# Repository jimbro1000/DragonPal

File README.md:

# PAL VIDEO BOARD FOR DRAGON 32 RECREATION Rev 3 #

To further improve video quality on the Dragon 32 this
board completely isolates the video circuits from the rest
of the Dragon by making it a plugin. This also means that
only a single version of the Dragon 32 board is needed to
provide a PAL or NTSC solution.

## Progress ##

This is a complete first hack at the design, while the
schematics are trusted the layout and organisation of the
line pulse logic is very much experimental.

The clock generator and analogue circuits are completely
isolated. The ground plane on the analogue side of the board 
is as complete and uniform as possible.

## To Do ##

Adopt the Dragon 64 voltage bias circuit for the output
signal

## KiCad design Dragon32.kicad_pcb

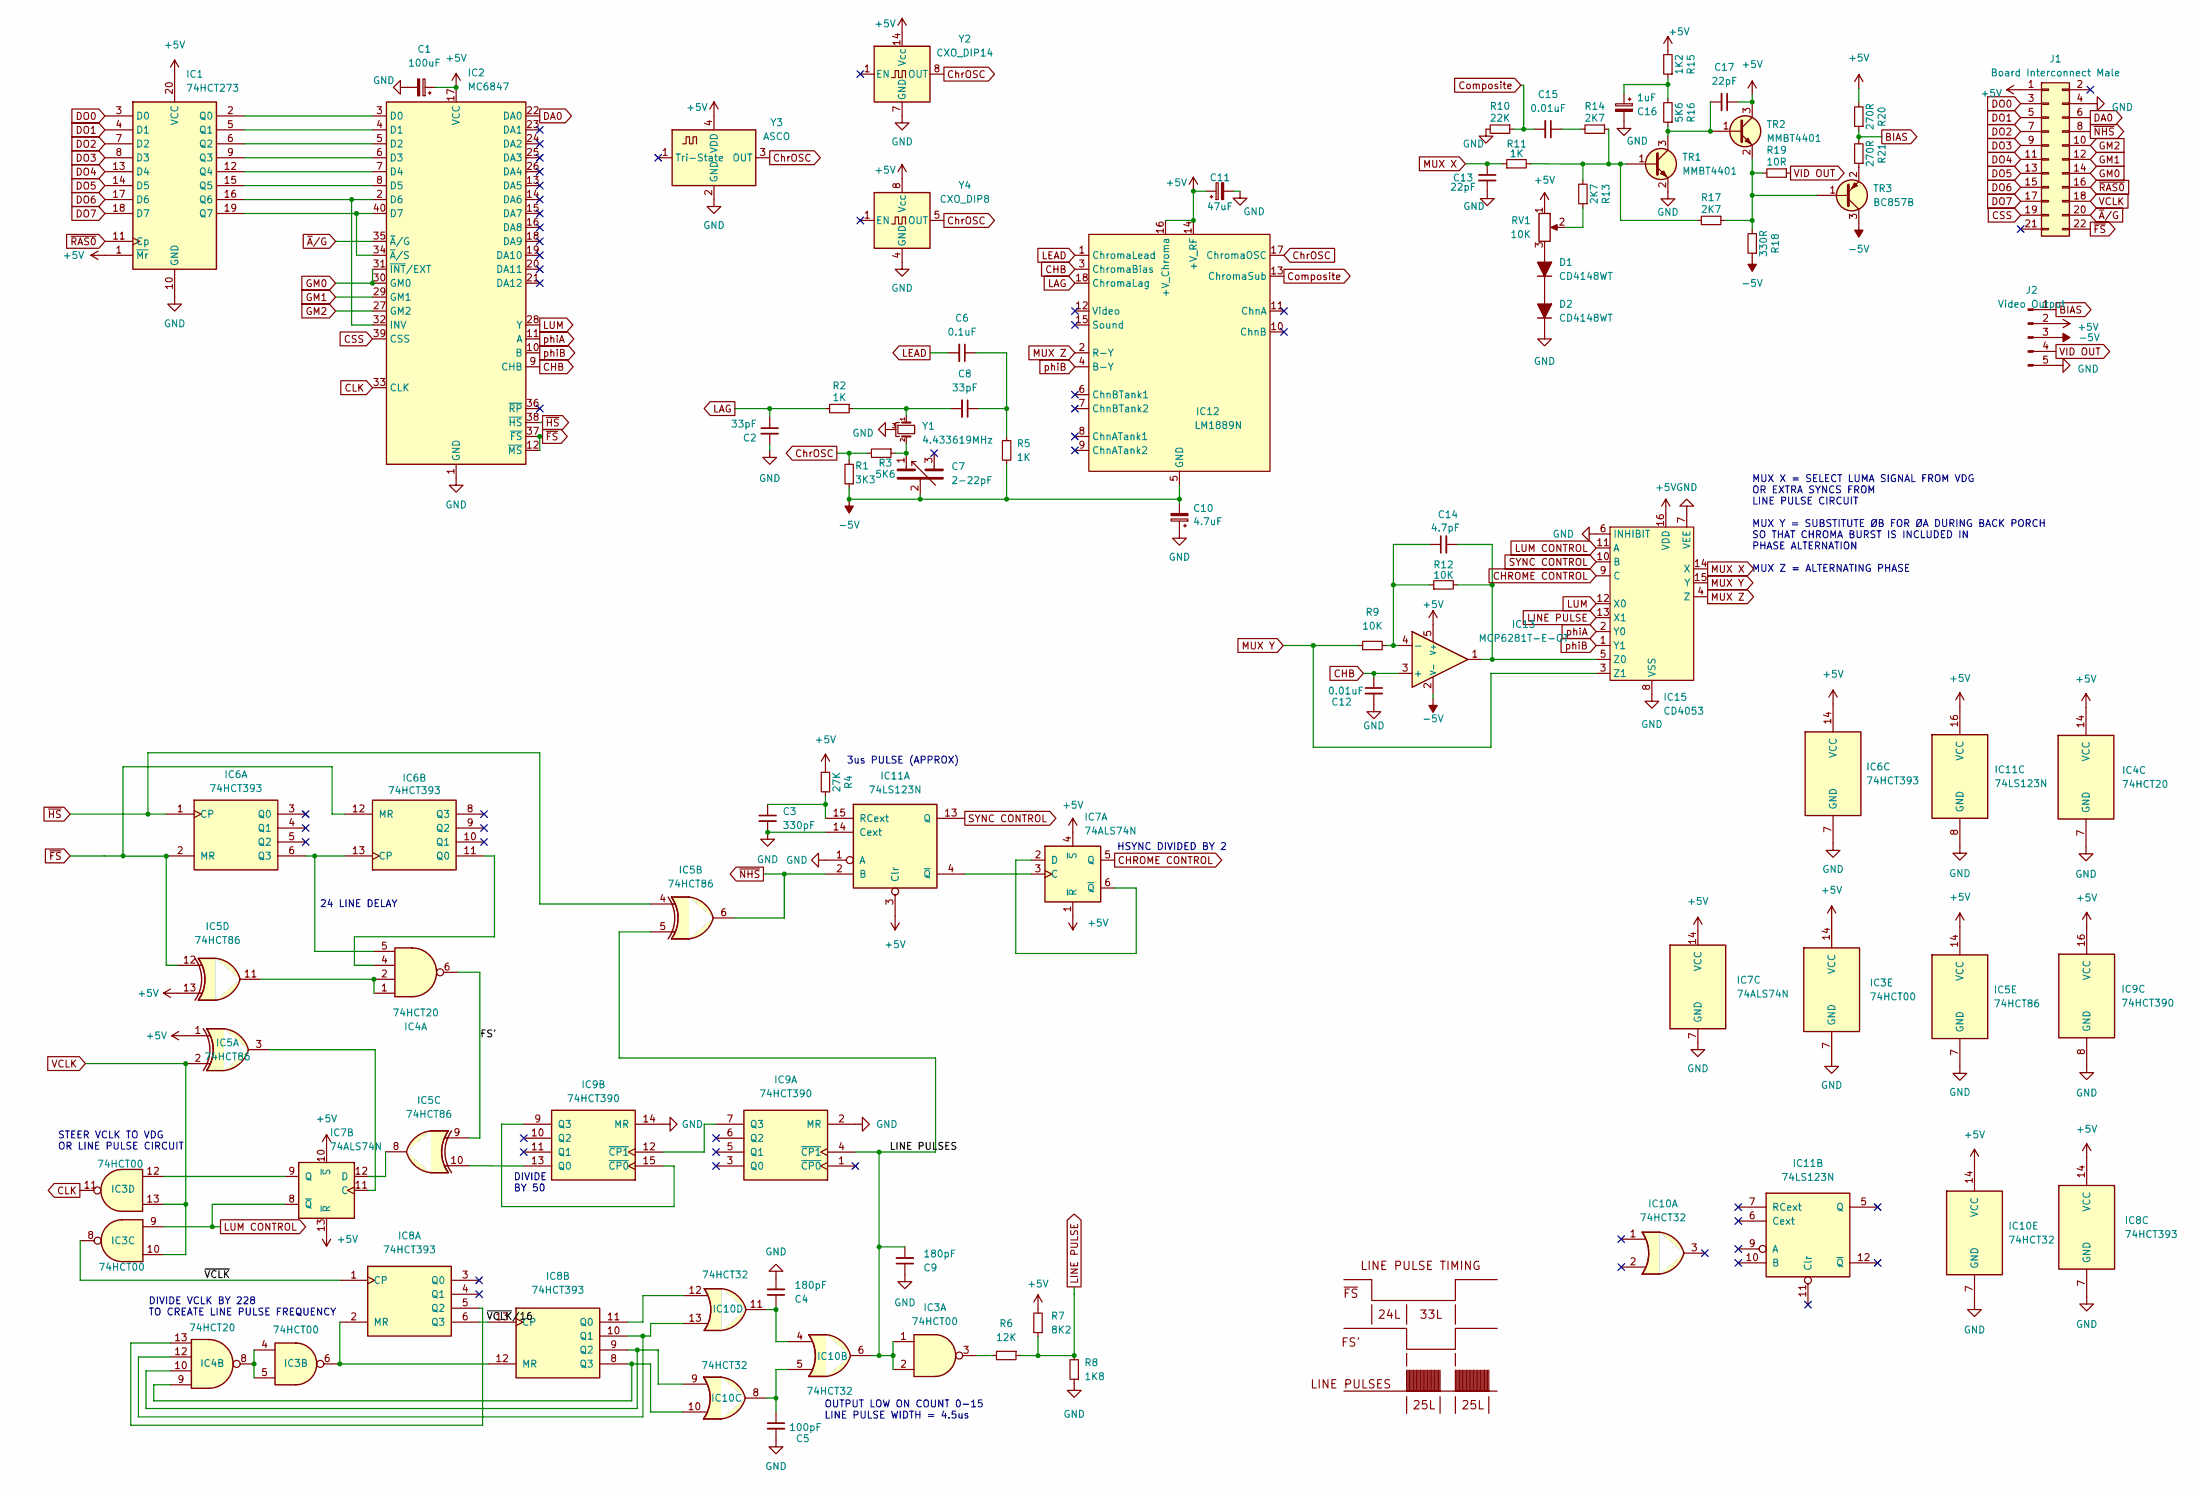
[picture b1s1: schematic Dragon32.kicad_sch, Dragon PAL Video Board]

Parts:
C1: 100uF; CP_Elec_6.3x5.8; DigiKey 732-8598-1-ND
C2, C8: 33pF; C_0603_1608Metric; LCSC C1663
C3: 330pF; C_0603_1608Metric; LCSC C1664
C4, C9: 180pF; C_0805_2012Metric_Pad1.18x1.45mm_HandSolder; DigiKey BC1016CT-ND
C5: 100pF; C_0805_2012Metric_Pad1.18x1.45mm_HandSolder; DigiKey 399-C316C101J5G5TA7303CT-ND
C6: 0.1uF; C_0805_2012Metric_Pad1.18x1.45mm_HandSolder; DigiKey BC1101CT-ND
C7: 2-22pF; Trimmer-7.5mm
C10: 4.7uF; CP_EIA-3528-15_AVX-H; DigiKey 478-3886-1-ND
C11: 47uF; CP_EIA-3528-15_AVX-H; DigiKey 478-11463-1-ND
C12, C15: 0.01uF; C_0805_2012Metric_Pad1.18x1.45mm_HandSolder; DigiKey BC2662CT-ND
C13, C17: 22pF; C_0805_2012Metric_Pad1.18x1.45mm_HandSolder; DigiKey 399-13930-1-ND
C14: 4.7pF; C_0603_1608Metric; DigiKey 445-180473-1-ND
C16: 1uF; CP_Elec_4x5.4; DigiKey 732-8966-1-ND
D1, D2: CD4148WT; D_0603_1608Metric; LCSC C30584800
IC1: 74HCT273; TSSOP-20_4.4x6.5mm_P0.65mm; DigiKey 296-8409-1-ND
IC2: MC6847; DIP-40_W15.24mm; LCSC C72123
IC3: 74HCT00; SOIC-14_3.9x8.7mm_P1.27mm; DigiKey 296-1626-ND
IC4: 74HCT20; SOIC-14_3.9x8.7mm_P1.27mm; DigiKey 296-3670-5-ND
IC5: 74HCT86; SOIC-14_3.9x8.7mm_P1.27mm; DigiKey 296-1669-5-ND
IC6, IC8: 74HCT393; SOIC-14_3.9x8.7mm_P1.27mm; DigiKey 296-14556-1-ND
IC7: 74ALS74N; SOIC-14_3.9x8.7mm_P1.27mm; DigiKey 296-1506-5-ND
IC9: 74HCT390; SOIC-16_3.9x9.9mm_P1.27mm; DigiKey 296-26516-5-ND
IC10: 74HCT32; SOIC-14_3.9x8.7mm_P1.27mm; DigiKey 296-1658-5-ND
IC11: 74LS123N; SOIC-16_3.9x9.9mm_P1.27mm; DigiKey 296-1636-5-ND
IC12: LM1889N; DIP-18_W7.62mm; LCSC C72116
IC13: MCP6281T-E-OT; SOT-23-5; LCSC C1347127
IC15: CD4053; SOIC-16_4.55x10.3mm_P1.27mm; DigiKey 296-2059-ND
J1: Board Interconnect Male; PinHeader_2x11_P2.54mm_Vertical
J2: Video Output; PinHeader_1x05_P2.54mm_Vertical
R1: 3K3; R_0805_2012Metric_Pad1.20x1.40mm_HandSolder; DigiKey CF14JT3K30CT-ND
R2, R5, R11: 1K; R_0805_2012Metric_Pad1.20x1.40mm_HandSolder; DigiKey CF14JT1K00CT-ND
R3, R16: 5K6; R_0805_2012Metric_Pad1.20x1.40mm_HandSolder; DigiKey CF14JT5K60CT-ND
R4: 27K; R_0805_2012Metric_Pad1.20x1.40mm_HandSolder; DigiKey CF14JT27K0CT-ND
R6: 12K; R_0805_2012Metric_Pad1.20x1.40mm_HandSolder; DigiKey CF14JT15K0CT-ND
R7: 8K2; R_0805_2012Metric_Pad1.20x1.40mm_HandSolder; DigiKey CF14JT6K80CT-ND
R8: 1K8; R_0805_2012Metric_Pad1.20x1.40mm_HandSolder; DigiKey CF14JT3K30CT-ND
R9, R12: 10K; R_0805_2012Metric_Pad1.20x1.40mm_HandSolder; DigiKey CF14JT10K0CT-ND
R10: 22K; R_0805_2012Metric_Pad1.20x1.40mm_HandSolder; DigiKey CF14JT22K0CT-ND
R13, R14, R17: 2K7; R_0805_2012Metric_Pad1.20x1.40mm_HandSolder; DigiKey CF14JT2K70CT-ND
R15: 1K2; R_0805_2012Metric_Pad1.20x1.40mm_HandSolder; DigiKey CF14JT1K20CT-ND
R18: 330R; R_0805_2012Metric_Pad1.20x1.40mm_HandSolder; DigiKey CF14JT330RCT-ND
R19: 10R; R_0805_2012Metric_Pad1.20x1.40mm_HandSolder; DigiKey CF14JT10R0CT-ND
R20, R21: 270R; R_0805_2012Metric_Pad1.20x1.40mm_HandSolder; DigiKey CF14JT270RCT-ND
RV1: 10K; Potentiometer_Bourns_3314J_Vertical; LCSC C36376
TR1, TR2: MMBT4401; SOT-23-3; DigiKey MMBT4401-FDICT-ND
TR3: BC857B; SOT-23-3; DigiKey BC857BLT1GOSCT-ND
Y1: 4.433619MHz; Crystal_HC49-U_Horizontal_1EP_style2
Y2: CXO_DIP14; Oscillator_DIP-14
Y3: ASCO; Oscillator_SMD_Abracon_ASV-4Pin_7.0x5.1mm_HandSoldering; LCSC C1883841
Y4: CXO_DIP8; Oscillator_DIP-8
Z1: LINE_PULSE_DIAGRAM

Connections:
+5V: C1.1, C11.1, C17.1, IC1.1 (~Mr), IC1.20 (VCC), IC2.17 (VCC), IC3.14 (VCC), IC4.14 (VCC), IC5.1, IC5.13, IC5.14 (VCC), IC6.14 (VCC), IC7.1 (~R), IC7.4 (~S), IC7.10 (~S), IC7.13 (~R), IC7.14 (VCC), IC8.14 (VCC), IC9.16 (VCC), IC10.14 (VCC), IC11.3 (Clr), IC11.16 (VCC), IC12.14 (+V_RF), IC12.16 (+V_Chroma), IC13.5 (V+), IC15.16 (VDD), J1.1, J2.2, R4.2, R7.2, R15.2, R20.2, RV1.1, TR2.3 (C), Y2.14 (Vcc), Y3.4 (VDD), Y4.8 (Vcc)
-5V: C7.2, C10.2, IC12.5 (GND), IC13.2 (V-), J2.3, R1.1, R5.2, R18.1, TR3.3 (C)
/FS': IC4.6, IC5.9
/LINE PULSES: C9.2, IC3.1, IC3.2, IC5.5, IC9.4 (~CP1), IC10.6
/~VCLK: IC3.8, IC8.1 (CP)
/~VCLK/16: IC8.6 (Q3), IC8.13 (CP)
BIAS: J2.1, R20.1, R21.2
CHB: C12.1, IC2.9 (CHB), IC12.3 (ChromaBias), IC13.3 (+)
CHROME CONTROL: IC7.5 (Q), IC15.9 (C)
CLK: IC2.33 (CLK), IC3.11
CSS: IC2.39 (CSS), J1.19
ChrOSC: IC12.17 (ChromaOSC), R1.2, R3.2, Y2.8 (OUT), Y3.3 (OUT), Y4.5 (OUT)
Composite: C15.2, IC12.13 (ChromaSub), R10.1
DA0: IC2.22 (DA0), J1.6
DO0: IC1.3 (D0), J1.3
DO1: IC1.4 (D1), J1.5
DO2: IC1.7 (D2), J1.7
DO3: IC1.8 (D3), J1.9
DO4: IC1.13 (D4), J1.11
DO5: IC1.14 (D5), J1.13
DO6: IC1.17 (D6), J1.15
DO7: IC1.18 (D7), J1.17
GM0: IC2.30 (GM0), IC2.31 (~INT/EXT), J1.14
GM1: IC2.29 (GM1), J1.12
GM2: IC2.27 (GM2), J1.10
GND: C1.2, C2.2, C3.2, C4.2, C5.2, C9.1, C10.1, C11.2, C12.2, C13.2, C16.2, D2.1 (K), IC1.10 (GND), IC2.1 (GND), IC3.7 (GND), IC4.7 (GND), IC5.7 (GND), IC6.7 (GND), IC7.7 (GND), IC8.7 (GND), IC9.2 (MR), IC9.8 (GND), IC9.14 (MR), IC10.7 (GND), IC11.1 (A), IC11.8 (GND), IC11.14 (Cext), IC15.6 (INHIBIT), IC15.7 (VEE), IC15.8 (VSS), J1.4, J2.5, R8.1, R10.2, TR1.2 (E), Y1.3, Y2.7 (GND), Y3.2 (GND), Y4.4 (GND)
LAG: C2.1, IC12.18 (ChromaLag), R2.2
LEAD: C6.2, IC12.1 (ChromaLead)
LINE PULSE: IC15.13 (X1), R6.1, R7.1, R8.2
LUM: IC2.28 (Y), IC15.12 (X0)
LUM CONTROL: IC3.9, IC7.8 (~Q), IC15.11 (A)
MUX X: C13.1, IC15.14 (X), R11.1
MUX Y: IC15.3 (Z1), IC15.15 (Y), R9.1
MUX Z: IC12.2 (R-Y), IC15.4 (Z)
unnamed: C4.1, IC10.4, IC10.11
unnamed: C5.1, IC10.5, IC10.8
unnamed: C6.1, C8.1, R5.1
unnamed: C7.1, R3.1, Y1.2
unnamed: C8.2, R2.1, Y1.1
unnamed: C15.1, R14.2
unnamed: C16.1, R15.1, R16.2
unnamed: D1.2 (A), RV1.3
unnamed: D1.1 (K), D2.2 (A)
unnamed: IC1.2 (Q0), IC2.3 (D0)
unnamed: IC1.5 (Q1), IC2.4 (D1)
unnamed: IC1.6 (Q2), IC2.5 (D2)
unnamed: IC1.9 (Q3), IC2.6 (D3)
unnamed: IC1.12 (Q4), IC2.7 (D4)
unnamed: IC1.15 (Q5), IC2.8 (D5)
unnamed: IC1.16 (Q6), IC2.2 (D6), IC2.32 (INV)
unnamed: IC1.19 (Q7), IC2.34 (~A/S), IC2.40 (D7)
unnamed: IC3.3, R6.2
unnamed: IC3.4, IC3.5, IC4.8
unnamed: IC4.1, IC4.2, IC5.11
unnamed: IC4.5, IC6.6 (Q3), IC6.13 (CP)
unnamed: IC4.4, IC6.11 (Q0)
unnamed: IC7.2 (D), IC7.6 (~Q)
unnamed: IC5.3, IC7.11 (C)
unnamed: IC5.8, IC7.12 (D)
unnamed: IC3.12, IC7.9 (Q)
unnamed: IC3.6, IC8.2 (MR), IC8.12 (MR)
unnamed: IC4.13, IC8.5 (Q2)
unnamed: IC8.11 (Q0), IC10.12
unnamed: IC4.12, IC8.10 (Q1), IC10.13
unnamed: IC4.10, IC8.9 (Q2), IC10.9
unnamed: IC4.9, IC8.8 (Q3), IC10.10
unnamed: IC9.7 (Q3), IC9.12 (~CP1)
unnamed: IC5.10, IC9.13 (Q0)
unnamed: IC9.9 (Q3), IC9.15 (~CP0)
unnamed: C3.1, IC11.15 (RCext), R4.1
unnamed: IC7.3 (C), IC11.4 (~Q)
unnamed: C14.1, IC13.4 (-), R9.2, R12.1
unnamed: C14.2, IC13.1, IC15.5 (Z0), R12.2
unnamed: R13.1, RV1.2
unnamed: R11.2, R13.2, R14.1, R17.2, TR1.1 (B)
unnamed: C17.2, R16.1, TR1.3 (C), TR2.1 (B)
unnamed: R17.1, R18.2, R19.2, TR2.2 (E), TR3.1 (B)
unnamed: R21.1, TR3.2 (E)
SYNC CONTROL: IC11.13 (Q), IC15.10 (B)
VCLK: IC3.10, IC3.13, IC5.2, J1.18
VID OUT: J2.4, R19.1
phiA: IC2.11 (A), IC15.2 (Y0)
phiB: IC2.10 (B), IC12.4 (B-Y), IC15.1 (Y1)
~A/G: IC2.35 (~A/G), J1.20
~FS: IC2.12 (~MS), IC2.37 (~FS), IC5.12, IC6.2 (MR), IC6.12 (MR), J1.22
~HS: IC2.38 (~HS), IC5.4, IC6.1 (CP)
~NHS: IC5.6, IC11.2 (B), J1.8
~RAS0: IC1.11 (Cp), J1.16

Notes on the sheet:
24 LINE DELAY
MUX X = SELECT LUMA SIGNAL FROM VDG OR EXTRA SYNCS FROM LINE PULSE CIRCUIT MUX Y = SUBSTITUTE ØB FOR ØA DURING BACK PORCH SO THAT CHROMA BURST IS INCLUDED IN PHASE ALTERNATION MUX Z = ALTERNATING PHASE
3us PULSE (APPROX)
HSYNC DIVIDED BY 2
DIVIDE BY 50
DIVIDE VCLK BY 228 TO CREATE LINE PULSE FREQUENCY
STEER VCLK TO VDG OR LINE PULSE CIRCUIT
OUTPUT LOW ON COUNT 0-15 LINE PULSE WIDTH = 4.5us

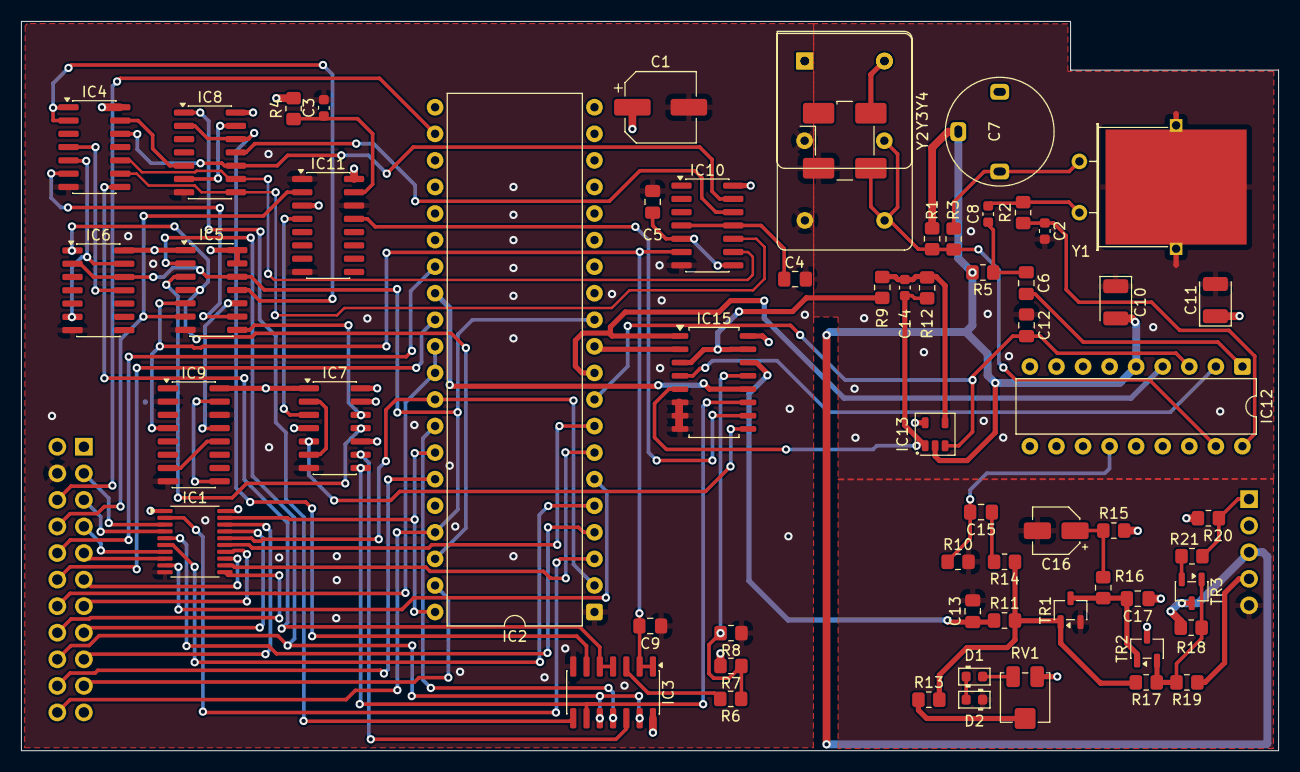
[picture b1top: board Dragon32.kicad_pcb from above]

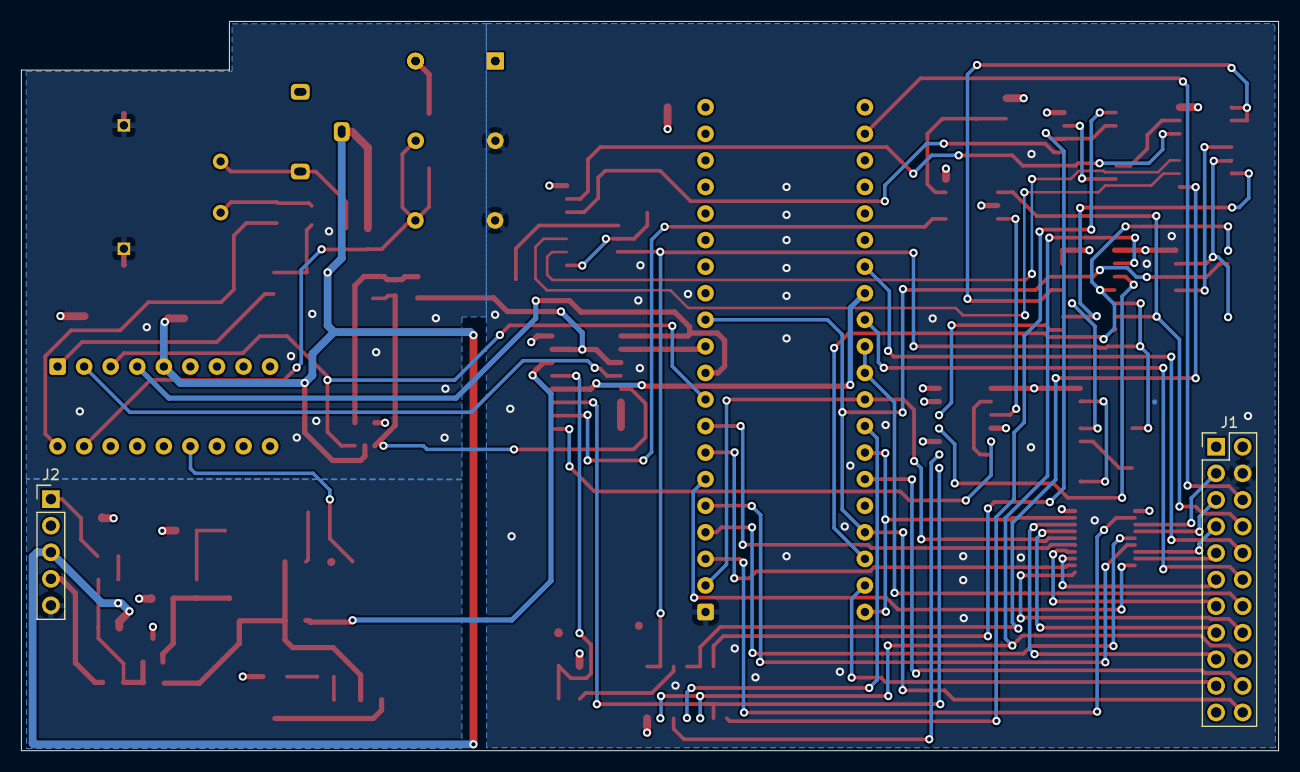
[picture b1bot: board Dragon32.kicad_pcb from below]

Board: 4 copper layers, 120.2 x 69.7 mm, 64 parts (2 on the bottom side), 88 nets.

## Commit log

2023-06-01 fix missing css and fs signals
2023-06-01 add render
2023-06-01 partial conversion
2023-06-02 complete traces
2023-06-10 fix diff amp wiring
2023-09-27 update render
2023-10-02 complete tracing for fabrication
2023-11-30 update board
2024-01-12 refresh ibom
2024-02-11 add test points
2024-02-11 revise layout
2024-02-11 notch edge of board for clearance of relay
2024-02-11 prep for fabrication
2024-03-04 move -5v
2024-03-16 trial ATF1504
2024-03-16 provide jtag connections
2024-04-03 tidy up routing
2024-04-03 fix transistor footprints
2024-04-04 reformat board
2024-05-11 supplement power filtering
2024-06-12 refinement
2025-05-17 convert to KiCad 8
2025-05-25 tweak
2025-11-20 redesign smd approach
